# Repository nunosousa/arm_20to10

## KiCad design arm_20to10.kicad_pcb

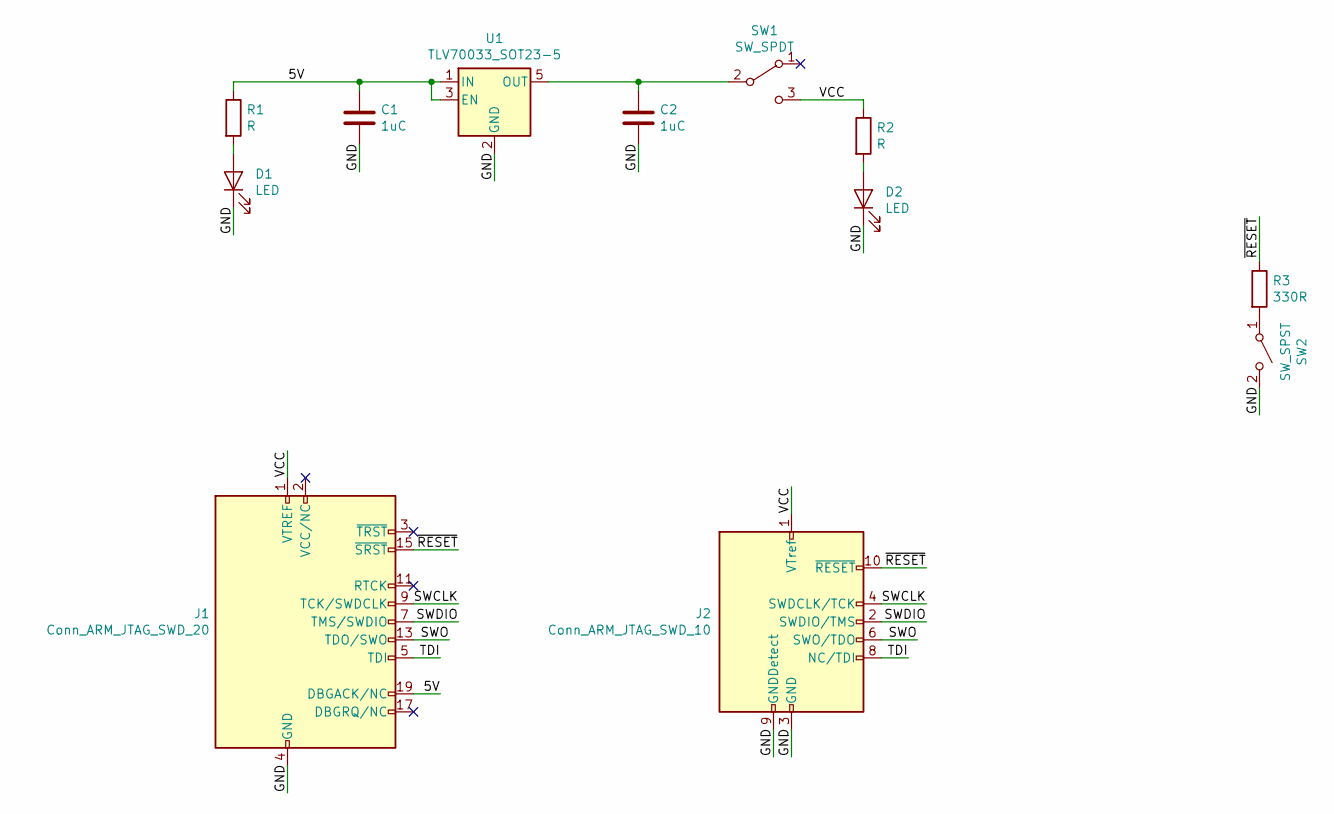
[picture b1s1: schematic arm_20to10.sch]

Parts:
C1, C2: 1uC; C_0805_2012Metric_Pad1.15x1.40mm_HandSolder
D1, D2: LED; LED_0805_2012Metric_Pad1.15x1.40mm_HandSolder
J1: Conn_ARM_JTAG_SWD_20; PinSocket_2x10_P2.54mm_Vertical; Manufacturer Part Number SFH11-PBPC-D10-ST-BK
J2: Conn_ARM_JTAG_SWD_10; PinHeader_2x05_P1.27mm_Vertical; Manufacturer Part Number 3220-10-0100-00
R1, R2: R; R_0805_2012Metric_Pad1.15x1.40mm_HandSolder
R3: 330R; R_0805_2012Metric_Pad1.15x1.40mm_HandSolder; Manufacturer Part Number CR0805-JW-331ELF
SW1: SW_SPDT; SW_CuK_JS202011AQN_DPDT_Angled; Manufacturer Part Number JS202011AQN
SW2: SW_SPST; SW_Tactile_Straight_KSA0Axx1LFTR; Manufacturer Part Number KSA0A311 LFTR
U1: TLV70033_SOT23-5; SOT-23-5; Manufacturer Part Number TLV70033DDCT

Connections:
/5V: C1.1, J1.19 (DBGACK/NC), R1.1, U1.1 (IN), U1.3 (EN)
/GND: C1.2, C2.2, D1.1 (K), D2.1 (K), J1.4 (GND), J1.6 (GND), J1.8 (GND), J1.10 (GND), J1.12 (GND), J1.14 (GND), J1.16 (GND), J1.18 (GND), J1.20 (GND), J2.3 (GND), J2.5 (GND), J2.9 (GNDDetect), SW2.2 (B), U1.2 (GND)
/SWCLK: J1.9 (TCK/SWDCLK), J2.4 (SWDCLK/TCK)
/SWDIO: J1.7 (TMS/SWDIO), J2.2 (SWDIO/TMS)
/SWO: J1.13 (TDO/SWO), J2.6 (SWO/TDO)
/TDI: J1.5 (TDI), J2.8 (NC/TDI)
/VCC: J1.1 (VTREF), J2.1 (VTref), R2.1, SW1.3 (C)
/~RESET: J1.15 (~SRST~), J2.10 (~RESET~), R3.1
unnamed: C2.1, SW1.2 (B), U1.5 (OUT)
unnamed: D1.2 (A), R1.2
unnamed: D2.2 (A), R2.2
unnamed: R3.2, SW2.1 (A)

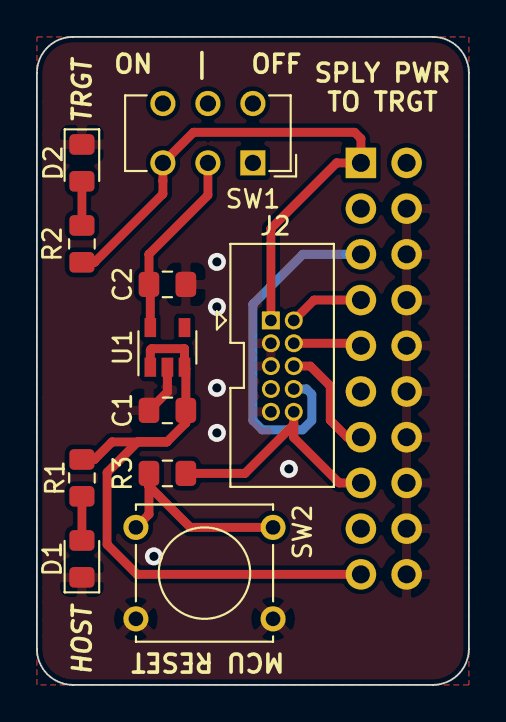
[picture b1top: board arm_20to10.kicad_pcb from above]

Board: 2 copper layers, 24.0 x 36.0 mm, 12 parts (1 on the bottom side), 12 nets.

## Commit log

2020-05-04 Updated circuit design.
2020-05-04 Removed not needed files.
2020-05-05 Progressed pcb layout.
2020-05-06 Final details.
2020-05-06 Final updates.
